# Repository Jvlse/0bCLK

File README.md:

# 0bCLK
11 LED Binary Clock using an ATmega48A, [Datasheet](ATmega48A-PA-88A-PA-168A-PA-328-P-DS-DS40002061A.pdf)

Code is [here](https://github.com/Jvlse/0bCLK/blob/main/CLK/main.c)

## FEATURES:
 - Binary Time on 11 LED's with PWM brightnesscontrol
 - Control over buttons
 - Sleepmode with shown reduce of power
 - Timebase using Timer and quartz crystal (accuracy can be messured at PB0)
 - Flashing using ISP, for example using a USBasp and avrdude or an Arduino

## Schematic:

## PCB:
 - I used a mill for the 2-layer PCB
 - All components are mounted on the top and soldered on the bottom
 - I used CR2032 battery cells
 - For orientation of the ISP: 
   - the square pad on the footprint is the VCC pin of the 6-pin ISP

## Command for flashing using avrdude in Windows: 
```avrdude -c [programmer] -p m48A -Uflash:w:Path\To\CLK\Debug\CLK.hex:i```

Example using USBasp, path is "C:\Atmel_Studio\7.0\CLK\Debug\CLK.hex":

```avrdude -c usbasp -p m48A -Uflash:w:C:\Atmel_Studio\7.0\CLK\Debug\CLK.hex:i```

## Power saving:
 - If CPU is doing nothing (waiting for Timer interrupt) 
   - goes to PWR_SAVE (basically completely off exept async Timer and interrupt)
 - Disabling individual Timers, Two Wire Interface (TWI), Universal Synchronous Asynchronous Receiver Transmitter (USART0) and Analog Digital Converter (ADC)
 - more optimizations: turning off Watchdog timer, brown out, lower CPU CLK, lower voltage, using sleepmodes

## Fuse bits:
 - SPIEN: LEAVE ON!
   - else it won't be flashable using SPI/ISP anymore
 - WDTON: OFF 
   - Watchdog timer not needed
 - CKDIV8: OFF
   - no system clock division needed
 - BODLEVEL: Maybe 
   - if left off a brown out might lead to malfunction

## Power usage:
 - Default 6,5mA -> 35h runtime
 - PWR_SAVE 1,2µA -> 191666h ~ 20 years runtime

## CLK inaccuracy:
 - Reasons:
   - No Capacitors at quartz crystal, quartz temperature (25°C is optimal)
 - Messuring:
   - Output of Pulse Per Second (PPS) Signal at PB0 and meassuring using a counter

## Timers:
 - Timer 0: every ms for PWM
 - Timer 2: every second for timebase

## Buttons:
 - PD0 -> down (PCINT16/RXD)
 - PD1 -> up (PCINT17/TXD)
 - PD2 -> mode (PCINT18/INT0)

## Ports: 
 - Data Direction Register:
   - DDR=0: Pin is input (button)
   - DDR=1: Pin is output (LED)
 - PORT-Register: 
   - if DDR=0 
     - 1: Pull-up resistor is active, for button
     - 0: Pull-up not active
   - if DDR=1 
     - 1: High voltage output
     - 0: Low voltage output

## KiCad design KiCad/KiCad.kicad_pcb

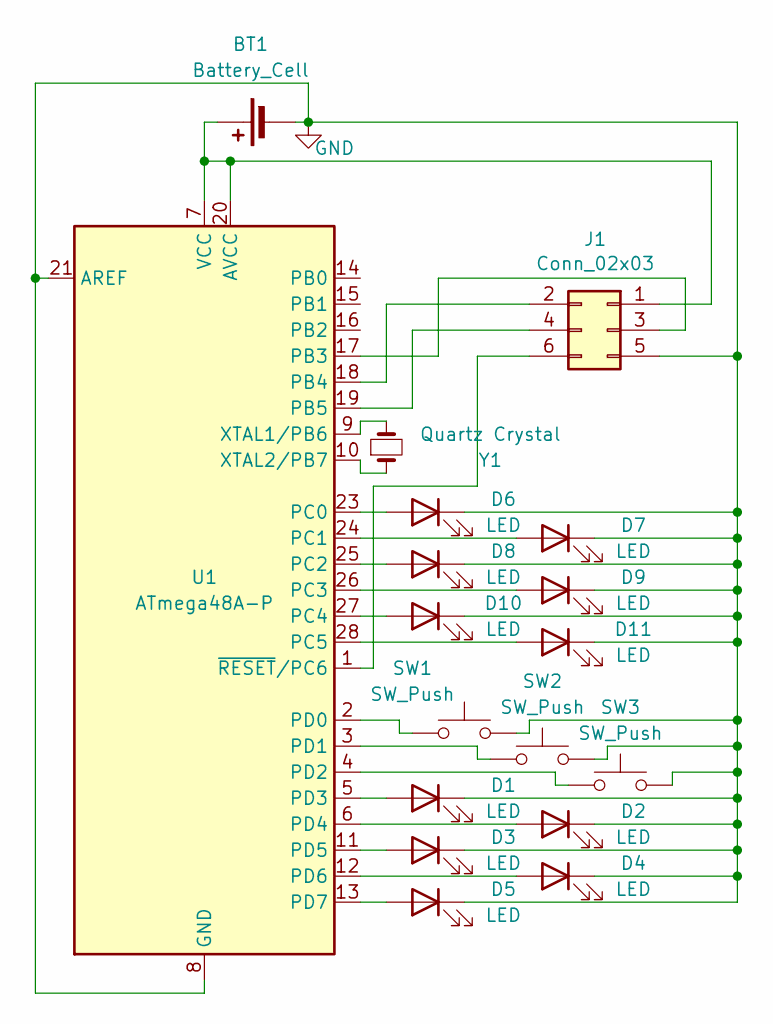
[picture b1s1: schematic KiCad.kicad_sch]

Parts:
BT1: Battery_Cell; BatteryHolder_Keystone_106_1x20mm
D1, D2, D3, D4, D5, D6, D7, D8, D9, D10, D11: LED; LED_D3.0mm
J1: Conn_02x03; PinSocket_2x03_P2.54mm_Vertical
SW1, SW2, SW3: SW_Push; SW_PUSH_1P1T_6x3.5mm_H5.0_APEM_MJTP1250
U1: ATmega48A-P; DIP-28_W7.62mm
Y1: Quartz Crystal; L_Radial_D6.0mm_P4.00mm

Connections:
GND: BT1.2 (-), D1.1 (K), D2.1 (K), D3.1 (K), D4.1 (K), D5.1 (K), D6.1 (K), D7.1 (K), D8.1 (K), D9.1 (K), D10.1 (K), D11.1 (K), J1.5, SW1.2, SW2.2, SW3.2, U1.8 (GND), U1.21 (AREF), U1.22 (GND)
unnamed: BT1.1 (+), J1.1, U1.7 (VCC), U1.20 (AVCC)
unnamed: D1.2 (A), U1.5 (PD3)
unnamed: D2.2 (A), U1.6 (PD4)
unnamed: D3.2 (A), U1.11 (PD5)
unnamed: D4.2 (A), U1.12 (PD6)
unnamed: D5.2 (A), U1.13 (PD7)
unnamed: D6.2 (A), U1.23 (PC0)
unnamed: D7.2 (A), U1.24 (PC1)
unnamed: D8.2 (A), U1.25 (PC2)
unnamed: D9.2 (A), U1.26 (PC3)
unnamed: D10.2 (A), U1.27 (PC4)
unnamed: D11.2 (A), U1.28 (PC5)
unnamed: J1.2, U1.18 (PB4)
unnamed: J1.3, U1.17 (PB3)
unnamed: J1.4, U1.19 (PB5)
unnamed: J1.6, U1.1 (~RESET/PC6)
unnamed: SW1.1, U1.2 (PD0)
unnamed: SW2.1, U1.3 (PD1)
unnamed: SW3.1, U1.4 (PD2)
unnamed: U1.9 (XTAL1/PB6), Y1.2
unnamed: U1.10 (XTAL2/PB7), Y1.1

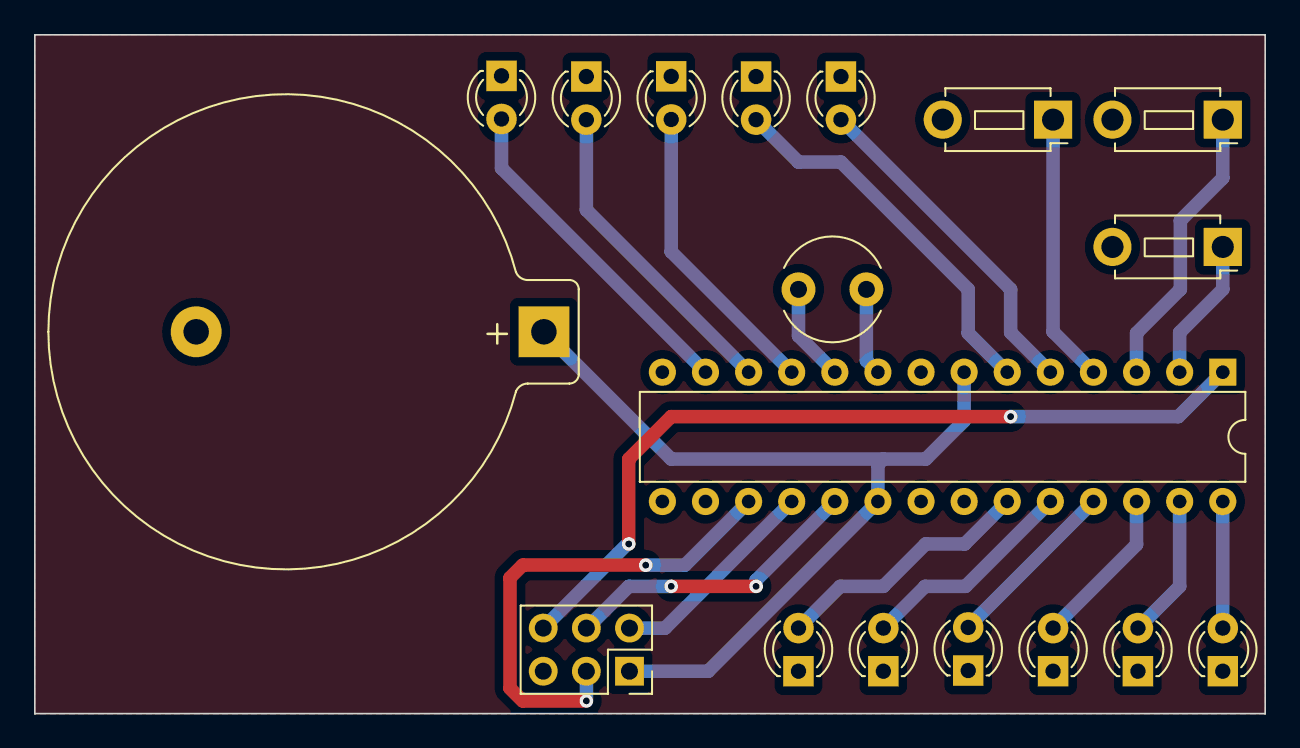
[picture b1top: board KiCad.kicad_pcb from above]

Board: 2 copper layers, 72.5 x 40.0 mm, 18 parts (0 on the bottom side), 22 nets.

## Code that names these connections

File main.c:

#define F_CPU 1000000UL
#include <avr/io.h>
#include <avr/interrupt.h>
#include <avr/sleep.h>
#include <avr/power.h>
#include <util/delay.h>

volatile uint8_t millisekunde=0;
volatile uint8_t sekunde=0;
volatile uint8_t minute=30;
volatile uint8_t stunde=7;
volatile uint8_t modus=0; // Wenn 0 Helligkeit, wenn 1 Minuten, 2 Stunde einstellen
volatile uint8_t button=0;
volatile uint8_t pwm_modus=0; // 0 dunkelster Modus, 5 hellster
volatile uint8_t tmp;
volatile uint8_t prell=0;
volatile uint8_t portdtmp = 0b00000111; // default is high because the pull-up

void PWM(void);

int main(void) {
	DDRC=(uint8_t)0b00111111; // Setzt Bits 0-5 im DDR von C Ports (DDC5) auf 1, pins sind Ausgang
	DDRD=(uint8_t)0b111111000; // Letzte 3 sind Buttons, erste 5 LEDS (PD7 NOCH NICHT ANGESCHLOSSEN)
	PORTD=(uint8_t)portdtmp; // Letzte 3 Pullup-Widerstände aktiviert für Buttons, letzte 5 sind high/low Pegel
		
	// Interrupt enable
	PCICR|=(1<<PCIE2); // PCIE2 Bit auf 1 setzen -> PCINT16 bis PCINT23 aktiviert aktiviert
	PCMSK2|=(1<<PCINT18) | (1<<PCINT17) | (1<<PCINT16);// PCINT16 und PCINT17 aktivieren
	
	GTCCR|=(1<<TSM) | (1<<PSRASY);  // General Timer/Counter Control Register
	// TSM -> Timer Synchronisation Mode: PSRASY bit wird nicht von hardware resetet, PSRASY -> Prescaler Reset für Timer 2
	// Wichtig um Timer ohne probleme einzustellen
	
	// Timer0 für PWM:
	TCCR0A|=(1<<WGM01); // CTC Modus
	TCCR0B|=(1<<CS01);  // Prescaler 8
	OCR0A=125-1; // TCNT0=4, dann ENDE counter -> 256*4/1000000 = 1024ms Intervall
	// OCR0A=(0xFF*temp)/100;
	TIMSK0|=(1<<OCIE0A);  // Enable Compare Interrupt
	TIMSK0|=(1<<TOIE0);   // Timer/Counter0 Interrupt Mask Register, TOIE0 -> Overflow Interrupt enable
	
	// ASYNCHRON? Zeitbasis generieren für Timer 2 (Quarz) -> Funktioniert im PWR_SAVE sleepmode
	ASSR|=(1<<AS2);		// Asynchron Mode einschalten, Timer 2 -> Quarz
	TCCR2A|=(1<<WGM21); // CTC Modus für Timer 2
	TCCR2B|=(1<<CS22) | (1<<CS21);  // Prescaler 256
	OCR2A=128-1; // -> 256*128/32768 = 1s Intervall
	TIMSK2|=(1<<OCIE2A);
	TIMSK2|=(1<<TOIE2);
	
	GTCCR&=~(1<<TSM); // Timer starten
	sei(); // Interrupts global erlauben, interrupt bit wird 0, setzt I-Bit in SREG auf 1
	
	// STROM SPAREN:
	sleep_enable();
	set_sleep_mode(SLEEP_MODE_PWR_SAVE);
	power_adc_disable();
	power_twi_disable();
	power_timer1_disable();
	power_usart0_disable();
	power_timer0_enable(); // Wenn im power save modus timer 0 enable um pwm zu nutzen
	
	sleep_mode();
	while(1) {
		if(pwm_modus==0) {
			set_sleep_mode(SLEEP_MODE_PWR_SAVE);
			sleep_mode();
		}
	}
}

// PWM
void PWM() {
	if((millisekunde<((pwm_modus)*5)-(4) || pwm_modus==3) && pwm_modus!=0) { // bei höchstem Modus wird led komplett eingeschaltet
		sleep_disable();
		tmp=minute;
		tmp = (tmp & 0xF0) >> 4 | (tmp & 0x0F) << 4;
		tmp = (tmp & 0xCC) >> 2 | (tmp & 0x33) << 2;
		tmp = (tmp & 0xAA) >> 1 | (tmp & 0x55) << 1;
		PORTC=(tmp>>2);
		PORTD=(stunde<<3)|0b00000111;
	} else {
		sleep_disable();
		if(modus!=1) {PORTC=0x00;}
		if(modus!=2) {PORTD=(0x00<<3)|0b00000111;}
	}
}

ISR(PCINT2_vect) { // Interruptserviceroutine für PCINT16, PCINT17 und PCINT18
	uint8_t changedbits;
	changedbits = PIND ^ portdtmp; // portänderung wird mit xor erkannt, aber nur jede 2. durch prell zugelassen, da drücken und loslassen zählt
	portdtmp = PIND;
	
	prell=(prell+1)%2;
	if(prell==0) {		
		if(changedbits & (1 << PD0)) // UNTEN / PCINT16 changed
		{
			switch(modus) {
				case 0: // HELLIGKEIT
				pwm_modus=(pwm_modus-1)%4;
				break;
				
				case 1: // STUNDE
				stunde--;
				if(stunde>24) { // Overflow (0xFF), weil stunde -1
					stunde=23;
				}
				break;
				
				case 2: // MINUTE
				minute--;
				if(minute>60) { // Overflow (0xFF), weil minute -1
					minute=59;
				}
				break;
			}
		}
		
		if(changedbits & (1 << PD1)) // OBEN / PCINT17 changed
		{
			switch(modus) {
				case 0: // Helligkeit
				pwm_modus=(pwm_modus+1)%4;
				if(pwm_modus==3) { // bei hellster stufe wird pwm und timer 1 komplett ausgeschaltet und PWR SAVE sleepmodi genutzt
					power_timer0_disable();
					// oder set_sleep_mode(SLEEP_MODE_PWR_SAVE);
				} else {
					power_timer0_enable();
					// oder set_sleep_mode(SLEEP_MODE_IDLE);
				}
				break;
				
				case 1: // Stunde
				stunde++;
				if(stunde==24) {
					stunde=0;
				}
				break;
				
				case 2: //Minute
				minute++;
				if(minute==60) {
					minute=0;
				}
				break;
			}
		}
		
		if(changedbits & (1 << PD2))
		{
			modus=(modus+1)%3; // PCINT18 changed
		}
	}
}

ISR(TIMER0_COMPA_vect) {
	millisekunde=(millisekunde+1)%23;
	PWM();
}

ISR(TIMER2_COMPA_vect) { // Bei Timer2 Compare, Zeitbasis generieren
	sekunde++;
	if(sekunde>=60) {
		sekunde=0;
		minute++;
		if(minute>=60) {
			minute=0;
			stunde++;
			if(stunde>=24) {stunde=0;}
		}
	}
	
	PORTB = PORTB ^ 0b00000001; // ausgabe von 0.5Hz an PB0
	PWM();
}

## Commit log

2024-11-16 main.c for programming using Microchip Studio
2024-11-16 Put everything in a Microchip Studio Project
2024-11-16 Added KiCad Project Schematic, PCB and images
2024-11-16 Modified README
2024-11-16 Changes to PCB
2024-11-16 Modify README
2025-04-30 Update main.c
    refactor
